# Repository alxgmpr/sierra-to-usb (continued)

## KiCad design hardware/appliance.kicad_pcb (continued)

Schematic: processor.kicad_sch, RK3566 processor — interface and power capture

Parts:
C801, C803, C805, C807, C809: 1uF; C_0603_1608Metric_Pad1.08x0.95mm_HandSolder; Voltage Rating 25V; MPN CL10B105KA8NNNC; LCSC C29936
C802, C804, C806, C808, C810, C811, C812, C815, C816, C817, C818, C819, C821: 100nF; C_0603_1608Metric_Pad1.08x0.95mm_HandSolder; Voltage Rating 25V; MPN CL10B104KA8NNNC; LCSC C1590
C820: 1nF; C_0603_1608Metric_Pad1.08x0.95mm_HandSolder; Tolerance 5%; Voltage Rating 50V; MPN CL10C102JB8NNNC; LCSC C163508
C822, C824: 22uF; C_1210_3225Metric_Pad1.33x2.70mm_HandSolder; Voltage Rating 25V; MPN CL32B226KAJNNNE; LCSC C309062
C823: 10uF; C_1206_3216Metric_Pad1.33x1.80mm_HandSolder; Voltage Rating 25V; MPN CL31B106KAHNNNE; LCSC C14860
Q801, Q802: MMBT3904,215; SOT-23_Handsoldering; MPN MMBT3904,215
R801, R802, R804: 10kR; R_0603_1608Metric_Pad0.98x0.95mm_HandSolder; Tolerance 1%; Power Rating 0.1W; MPN RC0603FR-0710KL; LCSC C98220
R803, R805: 100kR; R_0603_1608Metric_Pad0.98x0.95mm_HandSolder; Tolerance 1%; Power Rating 0.1W; MPN RC0603FR-07100KL; LCSC C14675
SW801: PROCESSOR RECOVERY; SW_SPST_TL3342; Contact Rating 12VDC 50mA; MPN TL3342F160QG; LCSC C2886898
SW802: PROCESSOR / PMIC RESET; SW_SPST_TL3342; Contact Rating 12VDC 50mA; MPN TL3342F160QG; LCSC C2886898
U801: RK3566; Sierra_RK3566_BGA565; MPN RK3566; LCSC C2943786

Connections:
3V3_MAIN: C817.1, U801.1D13 (VCCIO1), U801.1H18 (USB_AVDD1_3V3), U801.1J2 (USB_AVDD2_3V3), U801.1N8 (VCCIO7); also elsewhere on the board
CLK24_IN: U801.AD37 (XIN24M); also elsewhere on the board
DDR_A_CLKN: U801.B5 (AC24); also elsewhere on the board
DDR_A_CLKP: U801.A5 (AC23); also elsewhere on the board
DDR_A_DQS0N: U801.H1 (DDR_DQS0N_A); also elsewhere on the board
DDR_A_DQS0P: U801.H2 (DDR_DQS0P_A); also elsewhere on the board
DDR_A_DQS1N: U801.N2 (DDR_DQS1N_A); also elsewhere on the board
DDR_A_DQS1P: U801.N1 (DDR_DQS1P_A); also elsewhere on the board
DDR_B_CLKN: U801.B7 (AC9); also elsewhere on the board
DDR_B_CLKP: U801.A7 (AC0); also elsewhere on the board
DDR_B_DQS0N: U801.A12 (DDR_DQS0N_B); also elsewhere on the board
DDR_B_DQS0P: U801.A13 (DDR_DQS0P_B); also elsewhere on the board
DDR_B_DQS1N: U801.B17 (DDR_DQS1N_B); also elsewhere on the board
DDR_B_DQS1P: U801.A17 (DDR_DQS1P_B); also elsewhere on the board
DDR_SOC_RZQ: U801.1F3 (DDR_RZQ); also elsewhere on the board
DEBUG_UART_RX: U801.1V19 (GPIO0_D0_u); also elsewhere on the board
DEBUG_UART_TX: U801.1U18 (GPIO0_D1_u); also elsewhere on the board
EMMC_CLK_SOC: U801.A29 (GPIO1_C5_d); also elsewhere on the board
EMMC_CMD: U801.A27 (GPIO1_C4_u); also elsewhere on the board
EMMC_D0: U801.A32 (GPIO1_B4_u); also elsewhere on the board
EMMC_D1: U801.B27 (GPIO1_B5_u); also elsewhere on the board
EMMC_D2: U801.B32 (GPIO1_B6_u); also elsewhere on the board
EMMC_D3: U801.B29 (GPIO1_B7_u); also elsewhere on the board
EMMC_D4: U801.B33 (GPIO1_C0_u); also elsewhere on the board
EMMC_D5: U801.A30 (GPIO1_C1_u); also elsewhere on the board
EMMC_D6: U801.B30 (GPIO1_C2_u); also elsewhere on the board
EMMC_D7: U801.A33 (GPIO1_C3_u); also elsewhere on the board
EMMC_RESET_N: U801.1B16 (GPIO1_C7_d); also elsewhere on the board
EMMC_STROBE: U801.1A16 (GPIO1_C6_d); also elsewhere on the board
FLASH_VOL_SEL: U801.AF38 (GPIO0_A7_u); also elsewhere on the board
GND: C801.2, C802.2, C803.2, C804.2, C805.2, C806.2, C807.2, C808.2, C809.2, C810.2, C811.2, C812.2, C815.2, C816.2, C817.2, C818.2, C819.2, C820.2, C821.2, C822.2, C823.2, C824.2, Q801.2 (E), Q802.2 (E), R803.2, R805.2, SW801.2, SW802.2, U801.1A19 (SARADC_VIN3), U801.1B10 (VSS_30), U801.1B11 (VSS_31), U801.1B15 (VSS_32), U801.1B18 (SARADC_VIN2), U801.1B19 (VSS_33), U801.1C4 (VSS_34), U801.1C5 (VSS_35), U801.1C6 (VSS_36), U801.1C8 (VSS_37), U801.1C9 (VSS_38), U801.1C14 (VSS_39), U801.1C16 (VSS_40), U801.1C17 (SARADC_VIN1), U801.1C18 (VSS_41), U801.1D1 (VSS_42), U801.1D3 (VSS_43), U801.1D4 (DDR_AVSS), U801.1D10 (VSS_44), U801.1D14 (VSS_45), U801.1E3 (VSS_46), U801.1E8 (VSS_47), U801.1E10 (VSS_48), U801.1E14 (VSS_49), U801.1E15 (VSS_50), U801.1E17 (VSS_51), U801.1F6 (VSS_52), U801.1F7 (VSS_53), U801.1F8 (VSS_54), U801.1F9 (VSS_55), U801.1F10 (VSS_56), U801.1F15 (VSS_57), U801.1F16 (VSS_58), U801.1F20 (AVSS1_6), U801.1G3 (VSS_59), U801.1G6 (VSS_60), U801.1G7 (VSS_61), U801.1G8 (VSS_62), U801.1G9 (VSS_63), U801.1G10 (VSS_64), U801.1G11 (VSS_65), U801.1G12 (VSS_66), U801.1G14 (VSS_67), U801.1G16 (AVSS1_7), U801.1G18 (AVSS1_8), U801.1G19 (AVSS1_9), U801.1G20 (AVSS1_10), U801.1H1 (VSS_68), U801.1H2 (VSS_69), U801.1H6 (VSS_70), U801.1H11 (VSS_71), U801.1H12 (VSS_72), U801.1H13 (VSS_73), U801.1J1 (VSS_74), U801.1J5 (SYSPLL_AVSS), U801.1J6 (VSS_75), U801.1J8 (VSS_76), U801.1J9 (VSS_77), U801.1J11 (VSS_78), U801.1J12 (VSS_79), U801.1J13 (VSS_80), U801.1J16 (AVSS1_11), U801.1J18 (AVSS1_12), U801.1K2 (VSS_81), U801.1K3 (VSS_82), U801.1K4 (VSS_83), U801.1K5 (VSS_84), U801.1K6 (VSS_85), U801.1K8 (VSS_86), U801.1K9 (VSS_87), U801.1K11 (VSS_88), U801.1K12 (VSS_89), U801.1K13 (VSS_90), U801.1K14 (VSS_91), U801.1K15 (VSS_92), U801.1K18 (AVSS1_13), U801.1L3 (VSS_93), U801.1L6 (VSS_94), U801.1L10 (VSS_95), U801.1L11 (VSS_96), U801.1L12 (VSS_97), U801.1L13 (VSS_98), U801.1L14 (VSS_99), U801.1L15 (VSS_100), U801.1L19 (AVSS1_14), U801.1M3 (VSS_101), U801.1M4 (VSS_102), U801.1M5 (VSS_103), U801.1M6 (VSS_104), U801.1M10 (VSS_105), U801.1M11 (VSS_106), U801.1M12 (VSS_107), U801.1M13 (VSS_108), U801.1M14 (VSS_109), U801.1M15 (VSS_110), U801.1M16 (VSS_111), U801.1M17 (VSS_112), U801.1M20 (VSS_113), U801.1N3 (VSS_114), U801.1N4 (VSS_115), U801.1N7 (VSS_116), U801.1N11 (AVSS_9), U801.1N12 (AVSS_10), U801.1N17 (PMUPLL_AVSS), U801.1P1 (VSS_117), U801.1P5 (VSS_118), U801.1P6 (VSS_119), U801.1P7 (VSS_120), U801.1P8 (AVSS_11), U801.1P10 (AVSS_12), U801.1P14 (AVSS_13), U801.1P15 (VSS_121), U801.1R3 (VSS_122), U801.1R4 (VSS_123), U801.1R5 (VSS_124), U801.1R6 (VSS_125), U801.1R7 (VSS_126), U801.1R8 (AVSS_14), U801.1R9 (AVSS_15), U801.1R11 (AVSS_16), U801.1R12 (AVSS_17), U801.1R13 (AVSS_18), U801.1R14 (AVSS_19), U801.1R15 (AVSS_20), U801.1T3 (VSS_127), U801.1T5 (VSS_128), U801.1T7 (AVSS_21), U801.1T8 (AVSS_22), U801.1T9 (AVSS_23), U801.1T10 (AVSS_24), U801.1T11 (AVSS_25), U801.1T12 (AVSS_26), U801.1T13 (AVSS_27), U801.1T14 (AVSS_28), U801.1T15 (AVSS_29), U801.1T16 (AVSS_30), U801.1T17 (AVSS_31), U801.1U2 (VSS_129), U801.1U12 (AVSS_32), U801.1U13 (AVSS_33), U801.1U15 (AVSS_34), U801.1U17 (AVSS_35), U801.1V1 (VSS_130), U801.1V4 (VSS_131), U801.1V7 (AVSS_36), U801.1V12 (AVSS_37), U801.1V13 (AVSS_38), U801.1V18 (AVSS_39), U801.A1 (VSS_1), U801.A2 (VSS_2), U801.A38 (VSS_3), U801.AA2 (VSS_18), U801.AC37 (VSS_24), U801.AD2 (VSS_19), U801.AE37 (VSS_25), U801.AH37 (VSS_26), U801.AL37 (VSS_27), U801.AP2 (VSS_20), U801.AP8 (VSS_22), U801.AP13 (AVSS_1), U801.AP16 (AVSS_2), U801.AP19 (AVSS_3), U801.AP22 (AVSS_4), U801.AP25 (AVSS_5), U801.AP28 (AVSS_6), U801.AP31 (AVSS_7), U801.AP34 (AVSS_8), U801.AP37 (VSS_28), U801.AR1 (VSS_21), U801.AR38 (VSS_29), U801.B1 (VSS_4), U801.B2 (VSS_5), U801.B6 (VSS_6), U801.B11 (VSS_7), U801.B14 (VSS_8), U801.B18 (VSS_9), U801.B21 (VSS_10), U801.B28 (VSS_11), U801.B31 (VSS_12), U801.D2 (VSS_13), U801.E37 (VSS_23), U801.H37 (AVSS1_1), U801.J2 (VSS_14), U801.L2 (VSS_15), U801.L37 (AVSS1_2), U801.P37 (AVSS1_3), U801.U2 (VSS_16), U801.U37 (AVSS1_4), U801.W2 (VSS_17), U801.Y37 (AVSS1_5); also elsewhere on the board
LPDDR4_A0_A: U801.C2 (AC11); also elsewhere on the board
LPDDR4_A0_B: U801.A9 (AC13); also elsewhere on the board
LPDDR4_A1_A: U801.C1 (AC2); also elsewhere on the board
LPDDR4_A1_B: U801.B9 (AC6); also elsewhere on the board
LPDDR4_A2_A: U801.1C1 (AC15); also elsewhere on the board
LPDDR4_A2_B: U801.1B7 (AC18); also elsewhere on the board
LPDDR4_A3_A: U801.1B3 (AC12); also elsewhere on the board
LPDDR4_A3_B: U801.1B6 (AC4); also elsewhere on the board
LPDDR4_A4_A: U801.1B1 (AC14); also elsewhere on the board
LPDDR4_A4_B: U801.1A6 (AC19); also elsewhere on the board
LPDDR4_A5_A: U801.1A1 (AC16); also elsewhere on the board
LPDDR4_A5_B: U801.B8 (AC5); also elsewhere on the board
LPDDR4_CKE0_A: U801.B4 (AC22); also elsewhere on the board
LPDDR4_CKE0_B: U801.1A3 (AC10); also elsewhere on the board
LPDDR4_CS0n_A: U801.B3 (AC25); also elsewhere on the board
LPDDR4_CS0n_B: U801.1B5 (AC28); also elsewhere on the board
LPDDR4_DM0_A: U801.1E2 (DDR_DM0_A); also elsewhere on the board
LPDDR4_DM0_B: U801.1B8 (DDR_DM0_B); also elsewhere on the board
LPDDR4_DM1_A: U801.1G1 (DDR_DM1_A); also elsewhere on the board
LPDDR4_DM1_B: U801.1A11 (DDR_DM1_B); also elsewhere on the board
LPDDR4_DQ0_A: U801.G2 (DDR_DQ0_A); also elsewhere on the board
LPDDR4_DQ0_B: U801.B12 (DDR_DQ0_B); also elsewhere on the board
LPDDR4_DQ1_A: U801.F2 (DDR_DQ1_A); also elsewhere on the board
LPDDR4_DQ1_B: U801.B10 (DDR_DQ1_B); also elsewhere on the board
LPDDR4_DQ2_A: U801.F1 (DDR_DQ2_A); also elsewhere on the board
LPDDR4_DQ2_B: U801.1A8 (DDR_DQ2_B); also elsewhere on the board
LPDDR4_DQ3_A: U801.E1 (DDR_DQ3_A); also elsewhere on the board
LPDDR4_DQ3_B: U801.1A7 (DDR_DQ3_B); also elsewhere on the board
LPDDR4_DQ4_A: U801.M2 (DDR_DQ4_A); also elsewhere on the board
LPDDR4_DQ4_B: U801.B13 (DDR_DQ4_B); also elsewhere on the board
LPDDR4_DQ5_A: U801.K1 (DDR_DQ5_A); also elsewhere on the board
LPDDR4_DQ5_B: U801.1A10 (DDR_DQ5_B); also elsewhere on the board
LPDDR4_DQ6_A: U801.K2 (DDR_DQ6_A); also elsewhere on the board
LPDDR4_DQ6_B: U801.1B9 (DDR_DQ6_B); also elsewhere on the board
LPDDR4_DQ7_A: U801.1E1 (DDR_DQ7_A); also elsewhere on the board
LPDDR4_DQ7_B: U801.1A9 (DDR_DQ7_B); also elsewhere on the board
LPDDR4_DQ8_A: U801.P2 (DDR_DQ8_A); also elsewhere on the board
LPDDR4_DQ8_B: U801.B19 (DDR_DQ8_B); also elsewhere on the board
LPDDR4_DQ9_A: U801.R1 (DDR_DQ9_A); also elsewhere on the board
LPDDR4_DQ9_B: U801.A19 (DDR_DQ9_B); also elsewhere on the board
LPDDR4_DQ10_A: U801.R2 (DDR_DQ10_A); also elsewhere on the board
LPDDR4_DQ10_B: U801.A20 (DDR_DQ10_B); also elsewhere on the board
LPDDR4_DQ11_A: U801.T2 (DDR_DQ11_A); also elsewhere on the board
LPDDR4_DQ11_B: U801.B20 (DDR_DQ11_B); also elsewhere on the board
LPDDR4_DQ12_A: U801.M1 (DDR_DQ12_A); also elsewhere on the board
LPDDR4_DQ12_B: U801.A15 (DDR_DQ12_B); also elsewhere on the board
LPDDR4_DQ13_A: U801.1F2 (DDR_DQ13_A); also elsewhere on the board
LPDDR4_DQ13_B: U801.B15 (DDR_DQ13_B); also elsewhere on the board
LPDDR4_DQ14_A: U801.1F1 (DDR_DQ14_A); also elsewhere on the board
LPDDR4_DQ14_B: U801.1C10 (DDR_DQ14_B); also elsewhere on the board
LPDDR4_DQ15_A: U801.1G2 (DDR_DQ15_A); also elsewhere on the board
LPDDR4_DQ15_B: U801.B16 (DDR_DQ15_B); also elsewhere on the board
LPDDR4_RESETn: U801.1C7 (AC29); also elsewhere on the board
MCU_PROCESSOR_RECOVERY_ASSERT: R804.1; also elsewhere on the board
MCU_PROCESSOR_RESET_ASSERT: R802.1; also elsewhere on the board
MODEM_USB_DM: U801.1J20 (USB3_HOST1_DM); also elsewhere on the board
MODEM_USB_DP: U801.1J19 (USB3_HOST1_DP); also elsewhere on the board
MODEM_USB_RXN: U801.V37 (USB3_HOST1_SSRXN); also elsewhere on the board
MODEM_USB_RXP: U801.V38 (USB3_HOST1_SSRXP); also elsewhere on the board
MODEM_USB_TXN_SOC: U801.W38 (USB3_HOST1_SSTXN); also elsewhere on the board
MODEM_USB_TXP_SOC: U801.W37 (USB3_HOST1_SSTXP); also elsewhere on the board
MULTI_AVDD_0V9: U801.1K16 (MULTI_PHY_AVDD_0V9); also elsewhere on the board
MULTI_AVDD_1V8: U801.1K17 (MULTI_PHY_AVDD_1V8); also elsewhere on the board
unnamed: Q801.1 (B), R802.2, R803.1
unnamed: Q802.1 (B), R804.2, R805.1
PCIE_CLKREQ_N: U801.AG37 (GPIO0_A5_d); also elsewhere on the board
PCIE_PERST_SOC_N: U801.1R16 (GPIO0_B6_u); also elsewhere on the board
PCIE_REFCLK_N: U801.1K20 (PCIE20_REFCLKN); also elsewhere on the board
PCIE_REFCLK_P: U801.1K19 (PCIE20_REFCLKP); also elsewhere on the board
PCIE_RXN_SOC: U801.AB38 (PCIE20_RXN); also elsewhere on the board
PCIE_RXP_SOC: U801.AB37 (PCIE20_RXP); also elsewhere on the board
PCIE_TXN_SOC: U801.AA38 (PCIE20_TXN); also elsewhere on the board
PCIE_TXP_SOC: U801.AA37 (PCIE20_TXP); also elsewhere on the board
PCIE_WAKE_N: U801.1U20 (GPIO0_B5_u); also elsewhere on the board
PMIC_I2C_SCL: U801.AJ37 (GPIO0_B1_u); also elsewhere on the board
PMIC_I2C_SDA: U801.AK38 (GPIO0_B2_u); also elsewhere on the board
PMIC_INT_N: U801.1R19 (GPIO0_A3_u); also elsewhere on the board
PMIC_SLEEP: U801.1P19 (GPIO0_A2_d); also elsewhere on the board
RECOVERY_USB_DM: U801.R38 (USB_OTG0_DM); also elsewhere on the board
RECOVERY_USB_DP: U801.R37 (USB_OTG0_DP); also elsewhere on the board
RECOVERY_VBUS_DET: U801.T38 (USB_OTG0_VBUSDET); also elsewhere on the board
RK_RESET_N: Q801.3 (C), SW802.1, U801.AG38 (nPOR_u); also elsewhere on the board
SARADC_BOOT_KEY: C820.1, Q802.3 (C), R801.2, SW801.1, U801.1D17 (SARADC_VIN0)
SDMMC0_DET: U801.AF37 (GPIO0_A4_u); also elsewhere on the board
SOC_HEALTH: U801.AN37 (GPIO0_C4_d); also elsewhere on the board
TSADC_SHUTDOWN: U801.1R20 (GPIO0_A1_z); also elsewhere on the board
USB2_AVDD_0V9: U801.1J4 (USB_AVDD2_0V9); also elsewhere on the board
USB2_AVDD_1V8: U801.1J3 (USB_AVDD2_1V8); also elsewhere on the board
USB_AVDD_0V9: C815.1, U801.1J17 (USB_AVDD1_0V9); also elsewhere on the board
USB_AVDD_1V8: C816.1, U801.1H16 (USB_AVDD1_1V8); also elsewhere on the board
VCC3V3_PMU: C811.1, C812.1, U801.1N15 (PMUIO2), U801.1P16 (PMUIO1); also elsewhere on the board
VCCA1V8_PMU: C803.1, C804.1, U801.1N18 (PMUPLL_AVDD_1V8); also elsewhere on the board
VCCA_1V8: C807.1, C808.1, C818.1, C819.1, R801.1, U801.1D15 (OTP_VCC18), U801.1D16 (SARADC_AVDD_1V8), U801.1G17 (EDP_TX_AVDD_1V8), U801.1H4 (SYSPLL_AVDD_1V8), U801.1P9 (MIPI_CSI_RX_AVDD_1V8), U801.1P12 (MIPI_DSI_TX0_AVDD_1V8), U801.1P13 (HDMI_TX_AVDD_1V8), U801.1R10 (MIPI_DSI_TX1_AVDD_1V8); also elsewhere on the board
VCCIO_SD: U801.1F17 (VCCIO3); also elsewhere on the board
VCC_1V8: U801.1C13 (VCCIO2), U801.1E16 (VCCIO4), U801.1L4 (VCCIO6_1), U801.1L5 (VCCIO6_2), U801.1N5 (VCCIO5_1), U801.1N6 (VCCIO5_2); also elsewhere on the board
VDDA0V9_PMU: C801.1, C802.1, C809.1, C810.1, U801.1N16 (PMU_VDD_LOGIC_0V9), U801.1P17 (PMUPLL_AVDD_0V9); also elsewhere on the board
VDDA_0V9: C805.1, C806.1, U801.1H5 (SYSPLL_AVDD_0V9), U801.1H17 (EDP_TX_AVDD_0V9), U801.1N9 (MIPI_CSI_RX_AVDD_0V9), U801.1N10 (MIPI_DSI_TX1_AVDD_0V9), U801.1N13 (HDMI_TX_AVDD_0V9_2), U801.1N14 (HDMI_TX_AVDD_0V9_1), U801.1P11 (MIPI_DSI_TX0_AVDD_0V9); also elsewhere on the board
VDD_CPU: U801.1C12 (VDD_CPU_1), U801.1D11 (VDD_CPU_2), U801.1D12 (VDD_CPU_3), U801.1E11 (VDD_CPU_4), U801.1E12 (VDD_CPU_5), U801.1E13 (VDD_CPU_6), U801.1F11 (VDD_CPU_7), U801.1F12 (VDD_CPU_8), U801.1F13 (VDD_CPU_9), U801.1F14 (VDD_CPU_10), U801.1G13 (VDD_CPU_11); also elsewhere on the board
VDD_DDR_0V6: U801.1E6 (DDRPHY_VDDQL_1), U801.1E7 (DDRPHY_VDDQL_2), U801.1E9 (DDRPHY_VDDQL_3), U801.1F5 (DDRPHY_VDDQL_4), U801.1G5 (DDRPHY_VDDQL_5); also elsewhere on the board
VDD_DDR_1V1: U801.1D5 (DDRPHY_VDDQ_1), U801.1D6 (DDRPHY_VDDQ_2), U801.1D7 (DDRPHY_VDDQ_3), U801.1D8 (DDRPHY_VDDQ_4), U801.1D9 (DDRPHY_VDDQ_5), U801.1E4 (DDRPHY_VDDQ_6), U801.1F4 (DDRPHY_VDDQ_7), U801.1G4 (DDRPHY_VDDQ_8); also elsewhere on the board
VDD_GPU: U801.1L8 (VDD_GPU_1), U801.1L9 (VDD_GPU_2), U801.1M7 (VDD_GPU_3), U801.1M8 (VDD_GPU_4), U801.1M9 (VDD_GPU_5); also elsewhere on the board
VDD_LOGIC: U801.1H7 (VDD_LOGIC_1), U801.1H8 (VDD_LOGIC_2), U801.1H9 (VDD_LOGIC_3), U801.1H10 (VDD_LOGIC_4), U801.1J7 (VDD_LOGIC_5), U801.1J10 (VDD_LOGIC_6), U801.1K7 (VDD_LOGIC_7), U801.1K10 (VDD_LOGIC_8), U801.1L7 (VDD_LOGIC_9); also elsewhere on the board
VDD_NPU: C821.1, C822.1, C823.1, C824.1, U801.1G15 (VDD_NPU_1), U801.1H14 (VDD_NPU_2), U801.1H15 (VDD_NPU_3), U801.1J14 (VDD_NPU_4), U801.1J15 (VDD_NPU_5); also elsewhere on the board

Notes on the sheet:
PROCESSOR: 565 balls captured. CPU/eMMC/PCIe/USB and PMIC controls connected. Unused GPIO/analog signal balls are NC; disabled peripherals must remain disabled in firmware. TVSS and XOUT24M float per reference; 1.8V active oscillator feeds XIN24M. 1.8V flash strap, debug strap and thermal-shutdown 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

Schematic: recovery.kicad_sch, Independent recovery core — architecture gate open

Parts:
J101: 3.3V RAIL TEST; Wuerth_61300211121_1x02_P2.54mm_Vertical; MPN 61300211121
J102: CONTROL BOUNDARY; Wuerth_61301011121_1x10_P2.54mm_Vertical; MPN 61301011121

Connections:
+3V3: J101.1; also elsewhere on the board
/Recovery and always-on supply/POWER_FAULT_N: J102.9; also elsewhere on the board
/Recovery and always-on supply/SERVICE_RX: J102.7; also elsewhere on the board
/Recovery and always-on supply/SERVICE_TX: J102.6; also elsewhere on the board
ETH_PERST_N: J102.5; also elsewhere on the board
GND: J101.2, J102.10; also elsewhere on the board
MCU_ETH_POWER_EN: J102.2; also elsewhere on the board
MCU_HEALTH_IN: J102.8; also elsewhere on the board
MCU_MODEM_POWER_EN: J102.1; also elsewhere on the board
MODEM_OFF_N: J102.4; also elsewhere on the board
MODEM_RESET_N: J102.3; also elsewhere on the board

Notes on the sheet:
Service UART / health / fault inputs: 3.3V only. Add powered-off-safe translation when target voltage requires it. Service UART must not back-power target. No MCU modem-session interface is implemented.
SCOPE OF THIS SCHEMATIC MILESTONE
3.3V rail test; do not back-power. No PoE or unisolated input here.
Implemented: MCU, independent watchdog/brownout, SWD, manual reset, open-collector control outputs and default-off enables. Not implemented: packet processor, PoE/isolation, modem socket/SIM, high-current regulators or Ethernet. NOT a complete WAN appliance. J101 is a 3.3V rail test header; J102 is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

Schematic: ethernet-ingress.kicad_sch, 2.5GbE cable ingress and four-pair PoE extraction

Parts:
C1851, C1852, C1853, C1854: 100nF; C_0603_1608Metric_Pad1.08x0.95mm_HandSolder; Voltage Rating 25V; MPN CL10B104KA8NNNC
C1861, C1862, C1863, C1864: 10nF / 100V; C_0603_1608Metric_Pad1.08x0.95mm_HandSolder; Voltage Rating 100V; Tolerance 10%; MPN C1608X7R2A103K
C1865: 1nF / 2kV; C_1808_4520Metric_Pad1.72x2.30mm_HandSolder; Voltage Rating 2kV; MPN GR442QR73D102KW01L
D1851, D1852: TPD4E02B04DQAR; USON-10_2.5x1.0mm_P0.5mm; Working Voltage -3.6 to +3.6V; MPN TPD4E02B04DQAR; LCSC C106794
J1701: 2.5GbE + PoE; Sierra_RJE491881401_1x08-1MP_P1.02mm; Current Rating 1.25A per contact; MPN RJE491881401
R1861, R1862, R1863, R1864: 75R; R_0603_1608Metric_Pad0.98x0.95mm_HandSolder; Tolerance 1%; Power Rating 0.1W; MPN CRCW060375R0FKEA
T1701: HX4110NLT; Sierra_HX4110NL_2x12_P1.27mm; PoE Rating 4-pair 60W (manufacturer product finder); MPN HX4110NLT

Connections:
BOB_SMITH_COMMON: C1865.1, R1861.2, R1862.2, R1863.2, R1864.2
BS_PAIR0: C1861.2, R1861.1
BS_PAIR1: C1862.2, R1862.1
BS_PAIR2: C1863.2, R1863.1
BS_PAIR3: C1864.2, R1864.1
CABLE_MDI0_N: J1701.2, T1701.22 (MX1-)
CABLE_MDI0_P: J1701.1, T1701.23 (MX1+)
CABLE_MDI1_N: J1701.6, T1701.19 (MX2-)
CABLE_MDI1_P: J1701.3, T1701.20 (MX2+)
CABLE_MDI2_N: J1701.5, T1701.16 (MX3-)
CABLE_MDI2_P: J1701.4, T1701.17 (MX3+)
CABLE_MDI3_N: J1701.8, T1701.13 (MX4-)
CABLE_MDI3_P: J1701.7, T1701.14 (MX4+)
CHASSIS: C1865.2, J1701.SH
ETH_CT0: C1851.1, T1701.1 (TCT1)
ETH_CT1: C1852.1, T1701.4 (TCT2)
ETH_CT2: C1853.1, T1701.7 (TCT3)
ETH_CT3: C1854.1, T1701.10 (TCT4)
ETH_MDI0_N: D1851.2 (IO2), T1701.3 (TD1-); also elsewhere on the board
ETH_MDI0_P: D1851.1 (IO1), T1701.2 (TD1+); also elsewhere on the board
ETH_MDI1_N: D1851.5 (IO4), T1701.6 (TD2-); also elsewhere on the board
ETH_MDI1_P: D1851.4 (IO3), T1701.5 (TD2+); also elsewhere on the board
ETH_MDI2_N: D1852.2 (IO2), T1701.9 (TD3-); also elsewhere on the board
ETH_MDI2_P: D1852.1 (IO1), T1701.8 (TD3+); also elsewhere on the board
ETH_MDI3_N: D1852.5 (IO4), T1701.12 (TD4-); also elsewhere on the board
ETH_MDI3_P: D1852.4 (IO3), T1701.11 (TD4+); also elsewhere on the board
GND: C1851.2, C1852.2, C1853.2, C1854.2, D1851.3 (GND), D1851.8 (GND), D1852.3 (GND), D1852.8 (GND); also elsewhere on the board
POE_PAIR12: C1861.1, T1701.24 (MCT4); also elsewhere on the board
POE_PAIR36: C1862.1, T1701.21 (MCT2); also elsewhere on the board
POE_PAIR45: C1863.1, T1701.18 (MCT3); also elsewhere on the board
POE_PAIR78: C1864.1, T1701.15 (MCT4); also elsewhere on the board

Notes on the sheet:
T1701 pin/polarity and four center taps audited to Pulse page 2. PHY CTs: one 100nF to GND each, following RTL8125BG reference. Cable CTs feed active PoE bridge; 10nF series caps block PoE DC in Bob-Smith termination. CHASSIS is RJ45 shell/enclosure only. No copper connection across magnetics or to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

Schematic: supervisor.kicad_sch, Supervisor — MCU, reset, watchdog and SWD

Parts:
C201, C202, C204, C205: 100nF; C_0603_1608Metric_Pad1.08x0.95mm_HandSolder; Rating 25V X7R +/-10%; 0603; MPN CL10B104KA8NNNC; LCSC C1590
C203: 10uF; C_1206_3216Metric_Pad1.33x1.80mm_HandSolder; Rating 25V X7R +/-10%; bias margin reviewed; a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; MPN CL31B106KAHNNNE; LCSC C14860
J201: SWD / recovery; Wuerth_61300611121_1x06_P2.54mm_Vertical; MPN 61300611121
J202: WDT RUN jumper; Wuerth_61300211121_1x02_P2.54mm_Vertical; MPN 61300211121
R201, R202, R203: 10kR; R_0603_1608Metric_Pad0.98x0.95mm_HandSolder; Tolerance 1%; Power Rating 0.1W; MPN RC0603FR-0710KL; LCSC C98220
SW201: RESET; SW_SPST_TL3342; Contact Rating 12VDC 50mA; MPN TL3342F160QG; LCSC C2886898
U201: STM32G0B1CCT6; LQFP-48_7x7mm_P0.5mm; MPN STM32G0B1CCT6; LCSC C5270241
U202: TPS3828-33DBVR; SOT-23-5_HandSoldering; MPN TPS3828-33DBVR; LCSC C20032

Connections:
+3V3: C201.1, C202.1, C203.1, C204.1, J201.1, R201.1, R203.1, U201.4 (VBAT), U201.5 (VREF+), U201.6 (VDD), U202.5 (V_{DD}); also elsewhere on the board
/Recovery and always-on supply/ETH_RESET_ASSERT: U201.17 (PA6); also elsewhere on the board
/Recovery and always-on supply/MODEM_OFF_ASSERT: U201.16 (PA5); also elsewhere on the board
/Recovery and always-on supply/MODEM_RESET_ASSERT: U201.15 (PA4); also elsewhere on the board
/Recovery and always-on supply/POWER_FAULT_N: U201.20 (PB1); also elsewhere on the board
/Recovery and always-on supply/SERVICE_RX: U201.14 (PA3); also elsewhere on the board
/Recovery and always-on supply/SERVICE_TX: U201.13 (PA2); also elsewhere on the board
/Recovery and always-on supply/Supervisor/MANUAL_RESET_N: R203.2, SW201.1, U202.3 (~MR)
/Recovery and always-on supply/Supervisor/MCU_NRST_N: C205.1, J201.5, R201.2, U201.10 (PF2), U202.1 (~RESET)
/Recovery and always-on supply/Supervisor/SWCLK: J201.4, U201.36 (PA14)
/Recovery and always-on supply/Supervisor/SWDIO: J201.2, U201.35 (PA13)
/Recovery and always-on supply/Supervisor/WDT_INPUT: J202.2, U202.4 (WDI)
/Recovery and always-on supply/Supervisor/WDT_KICK: J202.1, R202.1, U201.19 (PB0)
GND: C201.2, C202.2, C203.2, C204.2, C205.2, J201.3, J201.6, R202.2, SW201.2, U201.7 (VSS), U202.2 (GND); also elsewhere on the board
MAIN3V3_GOOD: U201.44 (PB5); also elsewhere on the board
MAIN5V_GOOD: U201.46 (PB7); also elsewhere on the board
MCU_ETH_POWER_EN: U201.12 (PA1); also elsewhere on the board
MCU_HEALTH_IN: U201.18 (PA7); also elsewhere on the board
MCU_MAIN5V_EN: U201.45 (PB6); also elsewhere on the board
MCU_MODEM_POWER_EN: U201.11 (PA0); also elsewhere on the board
MCU_PROCESSOR_RECOVERY_ASSERT: U201.42 (PB3); also elsewhere on the board
MCU_PROCESSOR_RESET_ASSERT: U201.21 (PB2); also elsewhere on the board
MCU_PWRON_KICK: U201.43 (PB4); also elsewhere on the board
MODEM_BUCK_GOOD: U201.27 (PB15); also elsewhere on the board
MODEM_RAIL_GOOD: U201.25 (PB13); also elsewhere on the board
MODEM_SWITCH_GOOD: U201.26 (PB14); also elsewhere on the board
POE_BT_N: U201.24 (PB12); also elsewhere on the board
POE_TPH_N: U201.22 (PB10); also elsewhere on the board
POE_TPL_N: U201.23 (PB11); also elsewhere on the board

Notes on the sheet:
100nF at VDD/VREF; 10uF local bulk. No external clock required for UART/GPIO supervision.
PROGRAMMING / MANUAL RECOVERY
SUPERVISOR MCU — CONTROL ONLY
PF2 / pin 10 MUST remain NRST via option bytes. Internal BOR and IWDG enabled by protected boot firmware. PA2/PA3: USART2 AF1; PA13/PA14: SWD. UART is service only; no modem AT transport selected. Two signed app slots + protected loader planned; not implemented.
Fit RUN jumper for unattended use. Remove only for physical SWD service. WDI floats only with jumper removed.
VTref only; debugger must not power the target. Leave debug unlocked until signed-update recovery is proven. No USB data path through this MCU.
1.6s nominal watchdog; 2.93V threshold; 200ms nominal reset. Open-drain RESET directly shares MCU NRST with SWD. Verify NRST low-voltage margin across temperature before release.
EXTERNAL WATCHDOG + BROWNOUT

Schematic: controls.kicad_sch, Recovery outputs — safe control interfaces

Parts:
Q301, Q302, Q303: MMBT3904,215; SOT-23_Handsoldering; MPN MMBT3904,215
R301, R303, R305: 10kR; R_0603_1608Metric_Pad0.98x0.95mm_HandSolder; Tolerance 1%; Power Rating 0.1W; MPN RC0603FR-0710KL; LCSC C98220
R302, R304, R306, R307, R308: 100kR; R_0603_1608Metric_Pad0.98x0.95mm_HandSolder; Tolerance 1%; Power Rating 0.1W; MPN RC0603FR-07100KL; LCSC C14675

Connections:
/Recovery and always-on supply/ETH_RESET_ASSERT: R305.1; also elsewhere on the board
/Recovery and always-on supply/MODEM_OFF_ASSERT: R303.1; also elsewhere on the board
/Recovery and always-on supply/MODEM_RESET_ASSERT: R301.1; also elsewhere on the board
ETH_PERST_N: Q303.3 (C); also elsewhere on the board
GND: Q301.2 (E), Q302.2 (E), Q303.2 (E), R302.2, R304.2, R306.2, R307.2, R308.2; also elsewhere on the board
MCU_ETH_POWER_EN: R308.1; also elsewhere on the board
MCU_MODEM_POWER_EN: R307.1; also elsewhere on the board
MODEM_OFF_N: Q302.3 (C); also elsewhere on the board
MODEM_RESET_N: Q301.3 (C); also elsewhere on the board
unnamed: Q301.1 (B), R301.2, R302.1
unnamed: Q302.1 (B), R303.2, R304.1
unnamed: Q303.1 (B), R305.2, R306.1

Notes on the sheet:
INTEGRATION LIMITS
OPEN-COLLECTOR RESET / OFF — NO EXTERNAL PULL-UP TO ALWAYS-ON RAIL
POWER ENABLES — DEFAULT OFF ON MCU RESET
HIGH input asserts LOW output. Target pull-up / timing is profile-specific.
Reset outputs tolerate target pull-ups without sourcing voltage into an unpowered target. Maximum target sink current allocation: 1mA; verify low threshold with exact load. MODEM_OFF_N connects to FULL_CARD_POWER_OFF# only with a switched target-rail pull-up. Without that pull-up, the module remain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
Connect only to documented 3.3V-compatible enable inputs. The regulators / eFuses are NOT captured in this milestone.

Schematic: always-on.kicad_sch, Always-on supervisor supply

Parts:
C401: 4.7uF / 50V; C_1206_3216Metric_Pad1.33x1.80mm_HandSolder; MPN CL31B475KBHNNNE; LCSC C51205
C402, C403: 22uF / 25V; C_1210_3225Metric_Pad1.33x2.70mm_HandSolder; MPN CL32B226KAJNNNE; LCSC C309062
L401: 10uH; L_Coilcraft_LPS4018; MPN LPS4018-103MRC; LCSC C6127589
R401: 100kR; R_0603_1608Metric_Pad0.98x0.95mm_HandSolder; Tolerance 1%; Power Rating 0.1W; MPN RC0603FR-07100KL; LCSC C14675
U401: TPS62177DQCR; WSON-10-1EP_2x3mm_P0.5mm_EP0.84x2.4mm_ThermalVias; MPN TPS62177DQCR; LCSC C91241

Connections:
+3V3: C402.1, C403.1, L401.2, R401.1, U401.8 (~SLEEP), U401.10 (VOS); also elsewhere on the board
/Recovery and always-on supply/POWER_FAULT_N: R401.2, U401.7 (PG); also elsewhere on the board
GND: C401.2, C402.2, C403.2, U401.1 (PGND), U401.4 (NC), U401.5 (FB), U401.6 (AGND), U401.11 (PAD); also elsewhere on the board
ISO_12V: C401.1, U401.2 (VIN), U401.3 (EN); also elsewhere on the board
unnamed: L401.1, U401.9 (SW)

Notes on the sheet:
Independent supervisor supply
DRAFT: isolated 12V input; 3.3V / 0.5A output. No connection to raw PoE. EN tied to input; SLEEP tied to 3.3V for normal operation. Always on while the isolated input is present; downstream cuts must not gate this rail.
TI SLVSB35C, Figure 8 / Tables 2-3. 10uH + 2x22uF nominal. Capacitor DC bias, complete rail load and layout review remain open. Route VOS as Kelvin sense after L401; join AGND / PGND / exposed pad locally.

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
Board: 2 copper layers, 663 parts (0 on the bottom side), 378 nets, no tracks yet.

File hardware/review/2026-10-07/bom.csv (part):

Reference,Value,MPN,Manufacturer,Footprint,Default Assembly,Profile Rule,Datasheet,Release
J101,3.3V RAIL TEST,61300211121,Wuerth Elektronik,Recovery:Wuerth_61300211121_1x02_P2.54mm_Vertical,Fit,,https://www.we-online.com/components/products/datasheet/6130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,Engineering inventory; modem/footprint/electrical qualification pending
J102,CONTROL BOUNDARY,61301011121,Wuerth Elektronik,Recovery:Wuerth_61301011121_1x10_P2.54mm_Vertical,Fit,,https://www.we-online.com/components/products/datasheet/6130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,Engineering inventory; modem/footprint/electrical qualification pending
Q301,"MMBT3904,215","MMBT3904,215",Nexperia,Package_TO_SOT_SMD:SOT-23_Handsoldering,Fit,,https://assets.nexperia.com/documents/data-sheet/MMBT3904.pdf,Engineering inventory; modem/footprint/electrical qualification pending
Q302,"MMBT3904,215","MMBT3904,215",Nexperia,Package_TO_SOT_SMD:SOT-23_Handsoldering,Fit,,https://assets.nexperia.com/documents/data-sheet/MMBT3904.pdf,Engineering inventory; modem/footprint/electrical qualification pending
Q303,"MMBT3904,215","MMBT3904,215",Nexperia,Package_TO_SOT_SMD:SOT-23_Handsoldering,Fit,,https://assets.nexperia.com/documents/data-sheet/MMBT3904.pdf,Engineering inventory; modem/footprint/electrical qualification pending
R301,10kR,RC0603FR-0710KL,Yageo,Resistor_SMD:R_0603_1608Metric_Pad0.98x0.95mm_HandSolder,Fit,,https://www.yageo.com/upload/media/product/productsearch/dat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,Engineering inventory; modem/footprint/electrical qualification pending
R302,100kR,RC0603FR-07100KL,Yageo,Resistor_SMD:R_0603_1608Metric_Pad0.98x0.95mm_HandSolder,Fit,,https://www.yageo.com/upload/media/product/productsearch/dat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,Engineering inventory; modem/footprint/electrical qualification pending
R303,10kR,RC0603FR-0710KL,Yageo,Resistor_SMD:R_0603_1608Metric_Pad0.98x0.95mm_HandSolder,Fit,,https://www.yageo.com/upload/media/product/productsearch/dat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,Engineering inventory; modem/footprint/electrical qualification pending
R304,100kR,RC0603FR-07100KL,Yageo,Resistor_SMD:R_0603_1608Metric_Pad0.98x0.95mm_HandSolder,Fit,,https://www.yageo.com/upload/media/product/productsearch/dat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,Engineering inventory; modem/footprint/electrical qualification pending
R305,10kR,RC0603FR-0710KL,Yageo,Resistor_SMD:R_0603_1608Metric_Pad0.98x0.95mm_HandSolder,Fit,,https://www.yageo.com/upload/media/product/productsearch/dat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,Engineering inventory; modem/footprint/electrical qualification pending
R306,100kR,RC0603FR-07100KL,Yageo,Resistor_SMD:R_0603_1608Metric_Pad0.98x0.95mm_HandSolder,Fit,,https://www.yageo.com/upload/media/product/productsearch/dat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,Engineering inventory; modem/footprint/electrical qualification pending
R307,100kR,RC0603FR-07100KL,Yageo,Resistor_SMD:R_0603_1608Metric_Pad0.98x0.95mm_HandSolder,Fit,,https://www.yageo.com/upload/media/product/productsearch/dat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,Engineering inventory; modem/footprint/electrical qualification pending
R308,100kR,RC0603FR-07100KL,Yageo,Resistor_SMD:R_0603_1608Metric_Pad0.98x0.95mm_HandSolder,Fit,,https://www.yageo.com/upload/media/product/productsearch/dat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,Engineering inventory; modem/footprint/electrical qualification pending
C401,4.7uF / 50V,CL31B475KBHNNNE,Samsung Electro-Mechanics,Capacitor_SMD:C_1206_3216Metric_Pad1.33x1.80mm_HandSolder,Fit,,,Engineering inventory; modem/footprint/electrical qualification pending
C402,22uF / 25V,CL32B226KAJNNNE,Samsung Electro-Mechanics,Capacitor_SMD:C_1210_3225Metric_Pad1.33x2.70mm_HandSolder,Fit,,,Engineering inventory; modem/footprint/electrical qualification pending
C403,22uF / 25V,CL32B226KAJNNNE,Samsung Electro-Mechanics,Capacitor_SMD:C_1210_3225Metric_Pad1.33x2.70mm_HandSolder,Fit,,,Engineering inventory; modem/footprint/electrical qualification pending
L401,10uH,LPS4018-103MRC,Coilcraft,Inductor_SMD:L_Coilcraft_LPS4018,Fit,,https://www.coilcraft.com/getmedia/31b05c96-4c4c-4498-8dbb-f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,Engineering inventory; modem/footprint/electrical qualification pending
R401,100kR,RC0603FR-07100KL,Yageo,Resistor_SMD:R_0603_1608Metric_Pad0.98x0.95mm_HandSolder,Fit,,,Engineering inventory; modem/footprint/electrical qualification pending
U401,TPS62177DQCR,TPS62177DQCR,Texas Instruments,Package_SON:WSON-10-1EP_2x3mm_P0.5mm_EP0.84x2.4mm_ThermalVias,Fit,,https://www.ti.com/lit/ds/symlink/tps62175.pdf,Engineering inventory; modem/footprint/electrical qualification pending
C201,100nF,CL10B104KA8NNNC,Samsung Electro-Mechanics,Capacitor_SMD:C_0603_1608Metric_Pad1.08x0.95mm_HandSolder,Fit,,https://product.samsungsem.com/mlcc/CL10B104KA8NNN.do,Engineering inventory; modem/footprint/electrical qualification pending
C202,100nF,CL10B104KA8NNNC,Samsung Electro-Mechanics,Capacitor_SMD:C_0603_1608Metric_Pad1.08x0.95mm_HandSolder,Fit,,https://product.samsungsem.com/mlcc/CL10B104KA8NNN.do,Engineering inventory; modem/footprint/electrical qualification pending
C203,10uF,CL31B106KAHNNNE,Samsung Electro-Mechanics,Capacitor_SMD:C_1206_3216Metric_Pad1.33x1.80mm_HandSolder,Fit,,https://product.samsungsem.com/mlcc/CL31B106KAHNNN.do,Engineering inventory; modem/footprint/electrical qualification pending
C204,100nF,CL10B104KA8NNNC,Samsung Electro-Mechanics,Capacitor_SMD:C_0603_1608Metric_Pad1.08x0.95mm_HandSolder,Fit,,https://product.samsungsem.com/mlcc/CL10B104KA8NNN.do,Engineering inventory; modem/footprint/electrical qualification pending
C205,100nF,CL10B104KA8NNNC,Samsung Electro-Mechanics,Capacitor_SMD:C_0603_1608Metric_Pad1.08x0.95mm_HandSolder,Fit,,https://product.samsungsem.com/mlcc/CL10B104KA8NNN.do,Engineering inventory; modem/footprint/electrical qualification pending
J201,SWD / recovery,61300611121,Wuerth Elektronik,Recovery:Wuerth_61300611121_1x06_P2.54mm_Vertical,Fit,,https://www.we-online.com/components/products/datasheet/6130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,Engineering inventory; modem/footprint/electrical qualification pending
J202,WDT RUN jumper,61300211121,Wuerth Elektronik,Recovery:Wuerth_61300211121_1x02_P2.54mm_Vertical,Fit,,https://www.we-online.com/components/products/datasheet/6130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,Engineering inventory; modem/footprint/electrical qualification pending
R201,10kR,RC0603FR-0710KL,Yageo,Resistor_SMD:R_0603_1608Metric_Pad0.98x0.95mm_HandSolder,Fit,,https://www.yageo.com/upload/media/product/productsearch/dat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,Engineering inventory; modem/footprint/electrical qualification pending
R202,10kR,RC0603FR-0710KL,Yageo,Resistor_SMD:R_0603_1608Metric_Pad0.98x0.95mm_HandSolder,Fit,,https://www.yageo.com/upload/media/product/productsearch/dat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,Engineering inventory; modem/footprint/electrical qualification pending
R203,10kR,RC0603FR-0710KL,Yageo,Resistor_SMD:R_0603_1608Metric_Pad0.98x0.95mm_HandSolder,Fit,,https://www.yageo.com/upload/media/product/productsearch/dat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,Engineering inventory; modem/footprint/electrical qualification pending
SW201,RESET,TL3342F160QG,E-Switch,Button_Switch_SMD:SW_SPST_TL3342,Fit,,https://configured-product-images.s3.amazonaws.com/2D/specs/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,Engineering inventory; modem/footprint/electrical qualification pending
U201,STM32G0B1CCT6,STM32G0B1CCT6,STMicroelectronics,Package_QFP:LQFP-48_7x7mm_P0.5mm,Fit,,https://www.st.com/resource/en/datasheet/stm32g0b1cc.pdf,Engineering inventory; modem/footprint/electrical qualification pending
U202,TPS3828-33DBVR,TPS3828-33DBVR,Texas Instruments,Package_TO_SOT_SMD:SOT-23-5_HandSoldering,Fit,,https://www.ti.com/lit/ds/symlink/tps3828.pdf,Engineering inventory; modem/footprint/electrical qualification pending
C501,22uF / 25V,CL32B226KAJNNNE,Samsung Electro-Mechanics,Capacitor_SMD:C_1210_3225Metric_Pad1.33x2.70mm_HandSolder,Fit,,,Engineering inventory; modem/footprint/electrical qualification pending
C502,22uF / 25V,CL32B226KAJNNNE,Samsung Electro-Mechanics,Capacitor_SMD:C_1210_3225Metric_Pad1.33x2.70mm_HandSolder,Fit,,,Engineering inventory; modem/footprint/electrical qualification pending
C503,22uF / 25V,CL32B226KAJNNNE,Samsung Electro-Mechanics,Capacitor_SMD:C_1210_3225Metric_Pad1.33x2.70mm_HandSolder,Fit,,,Engineering inventory; modem/footprint/electrical qualification pending
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
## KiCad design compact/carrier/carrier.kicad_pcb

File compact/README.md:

# Compact USB-C modem carrier

The current design is [carrier/carrier.kicad_pro](carrier/carrier.kicad_pro), with a complete10-page schematic and a deliberately placed, entirely unrouted110×100mm PCB. Open it in KiCad10.99 or a compatible newer build. The original root project is preserved.

Start with [handoff artifacts](carrier/HANDOFF.md), [review and open gates](carrier/REVIEW.md), and [routing guide](carrier/ROUTING.md). The carrier has159 placed schematic components, zero ERC findings, zero parity findings and zero placement DRC violations;446 unconnected findings are intentional. No tracks, vias, filled copper or production Gerbers were created.

The design uses one USB-C port with3A current authorization, automatic USB3 orientation, module-powered nano-SIM, fixed vendor profiles, accessible controls and four edge SMA breakouts. Scope is EM9190 sub-6 and document-qualified RM520N-GL V1.0; RM551E is excluded. macOS networking remains a separate firmware/hardware test.

The4.0V input design has only69.8mW of calculated surplus under stated hot-loss allocations. It is a placement-stage prototype, not a fabrication-ready or bench-qualified design. Exact buck/socket sourcing, accepted stackup, CC configuration/readback, actual module/cooler/coax fit and all electrical/thermal/interface bench tests remain explicit gates in the review.

`energy-storage.kicad_sch` and the earlier TPS259470L/LTC3128/TPS62816 analyses are historical rejected candidates. Their passing subset checks do not apply to the current carrier. Current power calculations and source/compatibility records are under `review/`; final carrier checks and artifacts are under `carrier/build/`.

Generators use SHA-256 preflight guards. Preserve all generated/manual work; reconcile changes into generator sources rather than refreshing hashes to bypass a conflict. Once manual PCB routing starts, do not regenerate over it. Reproduction instructions are in the handoff index.

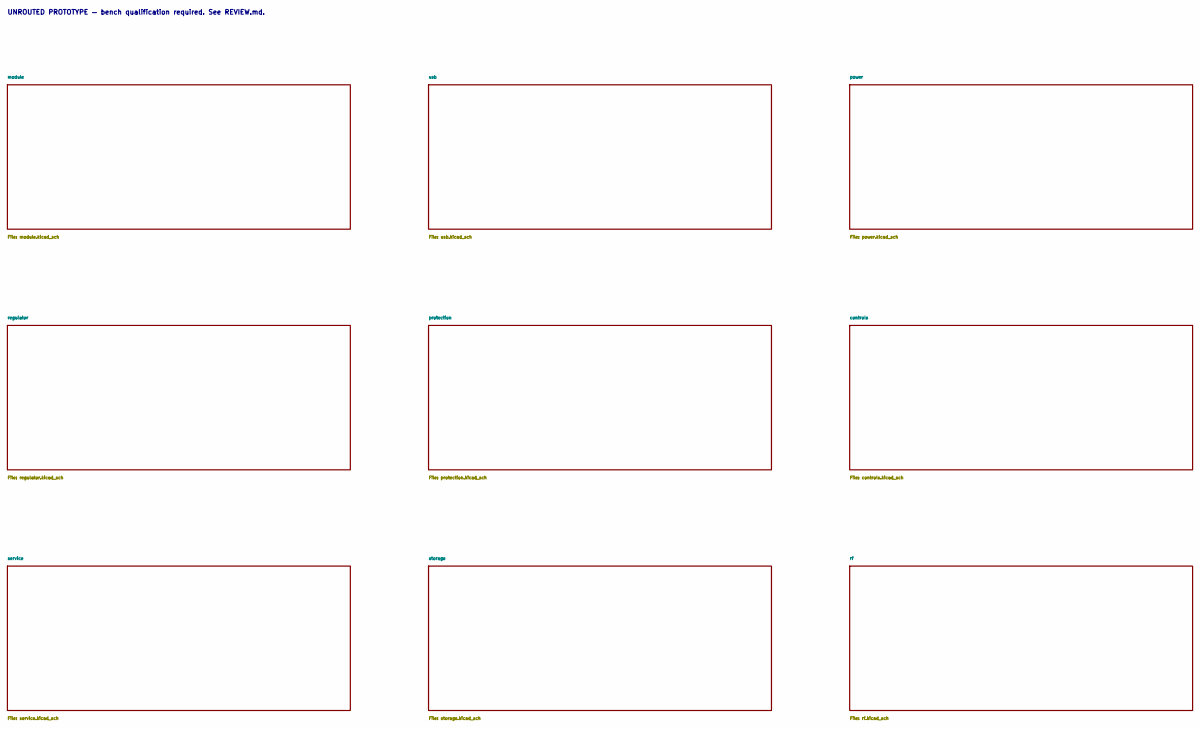
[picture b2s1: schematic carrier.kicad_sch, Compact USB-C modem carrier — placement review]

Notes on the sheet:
UNROUTED PROTOTYPE — bench qualification required. See REVIEW.md.
